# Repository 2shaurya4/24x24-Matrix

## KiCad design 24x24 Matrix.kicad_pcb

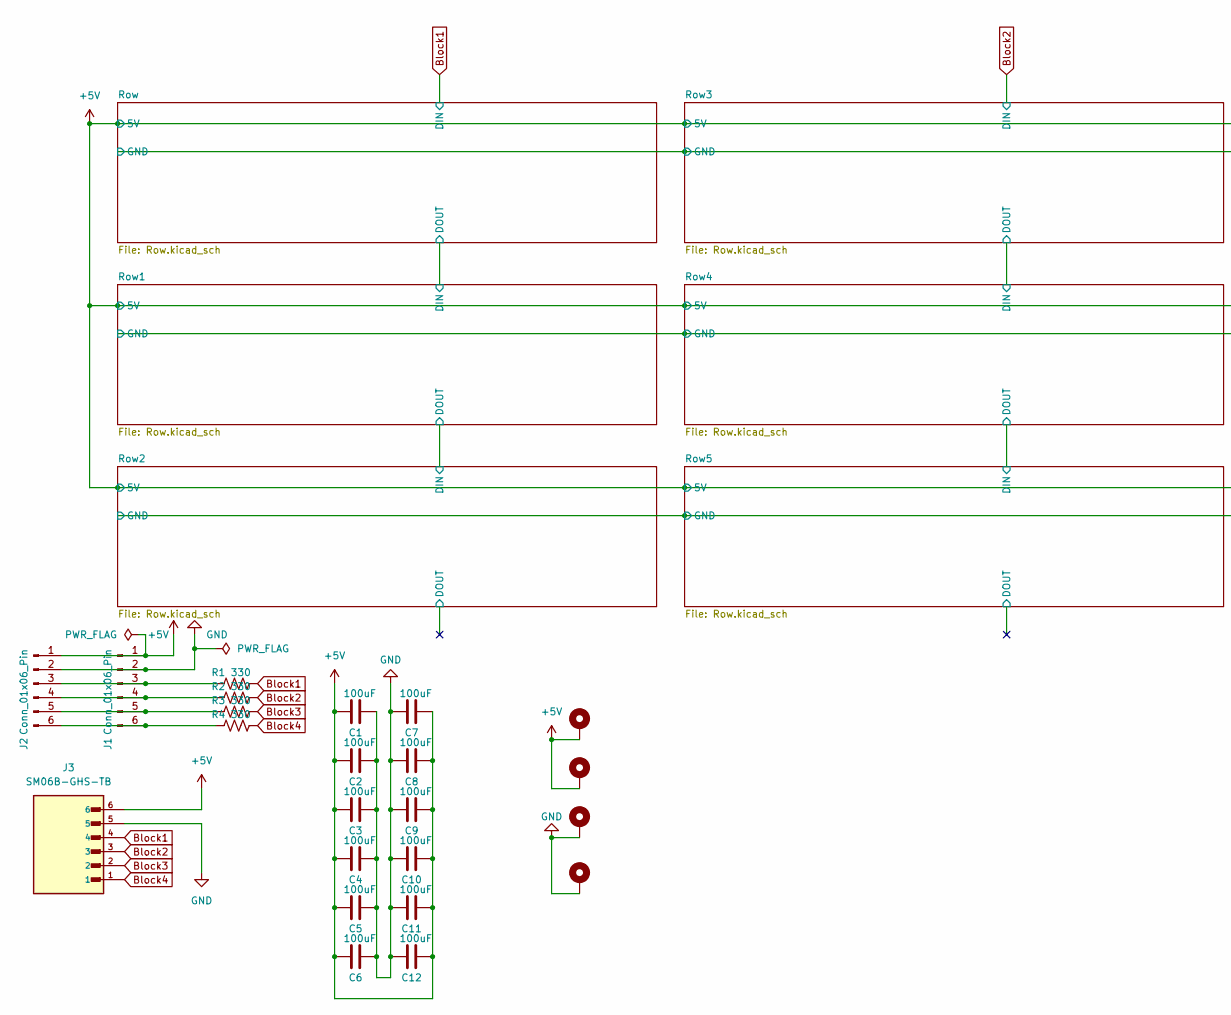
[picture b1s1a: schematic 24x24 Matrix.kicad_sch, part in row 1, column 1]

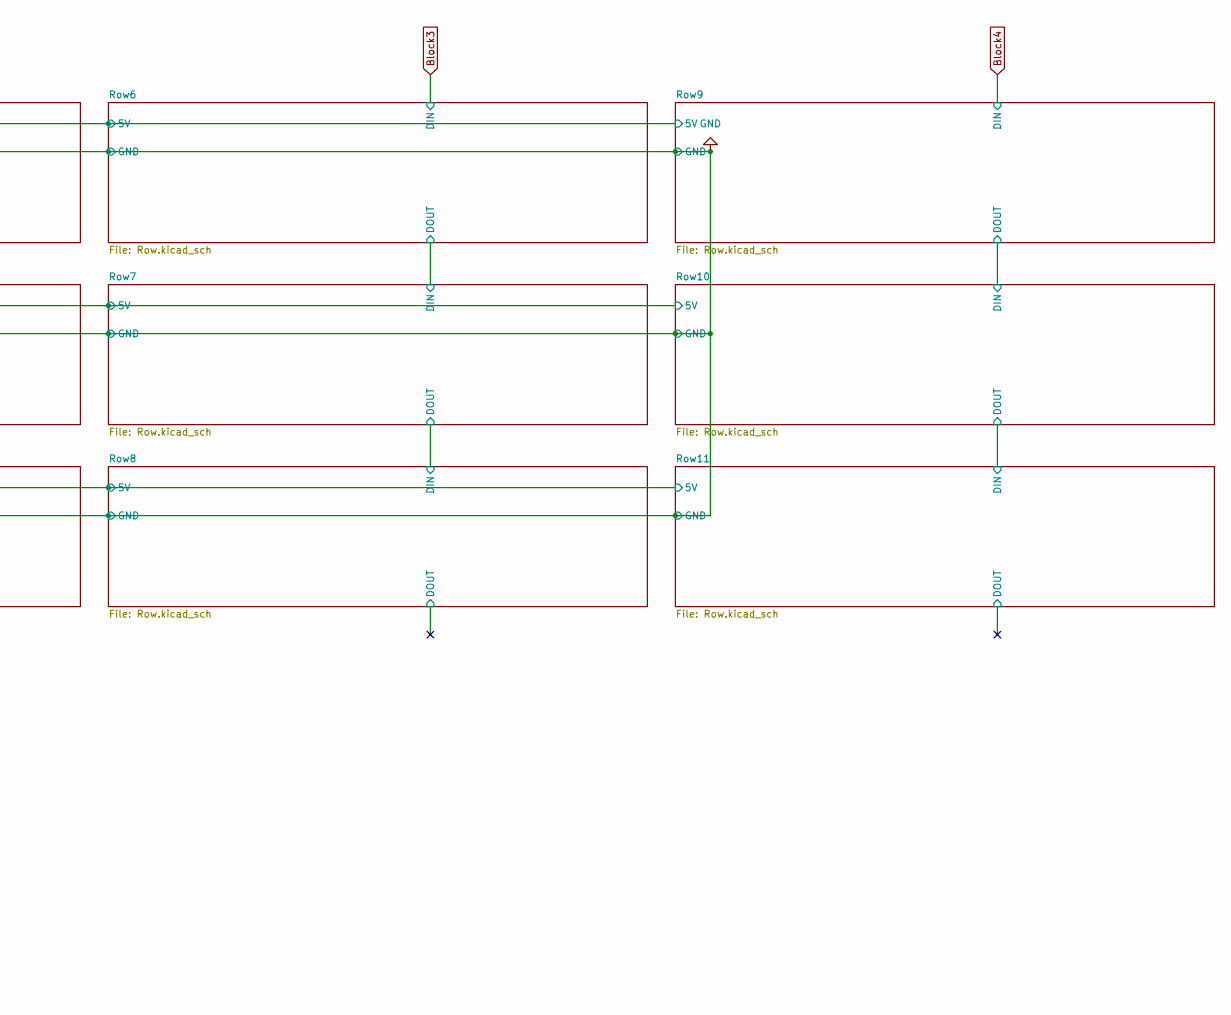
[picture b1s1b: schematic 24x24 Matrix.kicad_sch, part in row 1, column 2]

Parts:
C1, C2, C3, C4, C5, C6, C7, C8, C9, C10, C11, C12: 100uF; C_1206_3216Metric
H1, H2, H3, H4: MountingHole_Pad; MountingHole_2.7mm_M2.5_Pad_Via
J1, J2: Conn_01x06_Pin; PinHeader_1x06_P2.54mm_Vertical
J3: SM06B-GHS-TB; JST_SM06B-GHS-TB
R1, R2, R3, R4: 330; R_0402_1005Metric

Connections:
+5V: C1.1, C2.1, C3.1, C4.1, C5.1, C6.1, C7.2, C8.2, C9.2, C10.2, C11.2, C12.2, H1.1 (1_1), H2.1 (1_1), J1.1, J2.1, J3.6; also elsewhere on the board
Block1: J3.4, R1.2; also elsewhere on the board
Block2: J3.3, R2.2; also elsewhere on the board
Block3: J3.2, R3.2; also elsewhere on the board
Block4: J3.1, R4.2; also elsewhere on the board
GND: C1.2, C2.2, C3.2, C4.2, C5.2, C6.2, C7.1, C8.1, C9.1, C10.1, C11.1, C12.1, H3.1 (1_1), H4.1 (1_1), J1.2, J2.2, J3.5; also elsewhere on the board
unnamed: J1.3, J2.3, R1.1
unnamed: J1.4, J2.4, R2.1
unnamed: J1.5, J2.5, R3.1
unnamed: J1.6, J2.6, R4.1

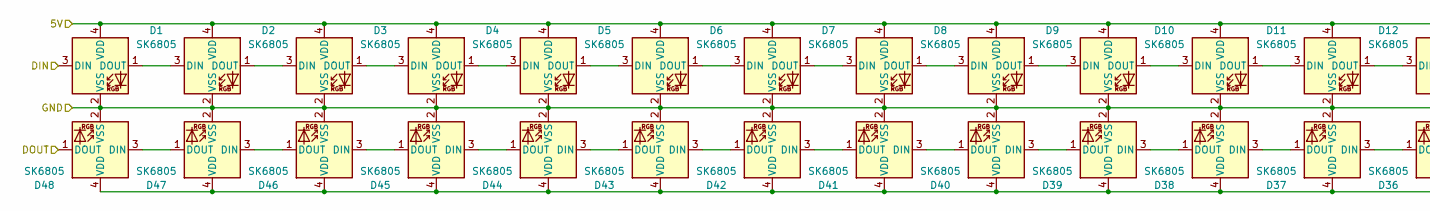
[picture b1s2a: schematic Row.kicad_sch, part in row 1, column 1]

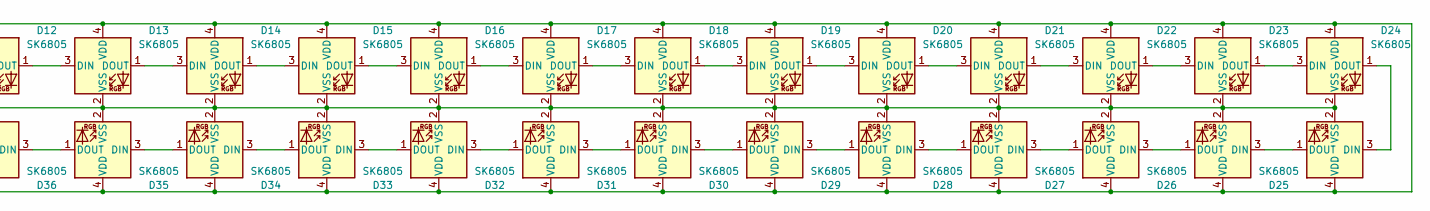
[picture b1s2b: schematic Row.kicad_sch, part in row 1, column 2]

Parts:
D1, D2, D3, D4, D5, D6, D7, D8, D9, D10, D11, D12, D13, D14, D15, D16, D17, D18, D19, D20, D21, D22, D23, D24, D25, D26, D27, D28, D29, D30, D31, D32, D33, D34, D35, D36, D37, D38, D39, D40, D41, D42, D43, D44, D45, D46, D47, D48: SK6805; LED_SK6812_EC15_1.5x1.5mm

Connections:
+5V: D1.4 (VDD), D2.4 (VDD), D3.4 (VDD), D4.4 (VDD), D5.4 (VDD), D6.4 (VDD), D7.4 (VDD), D8.4 (VDD), D9.4 (VDD), D10.4 (VDD), D11.4 (VDD), D12.4 (VDD), D13.4 (VDD), D14.4 (VDD), D15.4 (VDD), D16.4 (VDD), D17.4 (VDD), D18.4 (VDD), D19.4 (VDD), D20.4 (VDD), D21.4 (VDD), D22.4 (VDD), D23.4 (VDD), D24.4 (VDD), D25.4 (VDD), D26.4 (VDD), D27.4 (VDD), D28.4 (VDD), D29.4 (VDD), D30.4 (VDD), D31.4 (VDD), D32.4 (VDD), D33.4 (VDD), D34.4 (VDD), D35.4 (VDD), D36.4 (VDD), D37.4 (VDD), D38.4 (VDD), D39.4 (VDD), D40.4 (VDD), D41.4 (VDD), D42.4 (VDD), D43.4 (VDD), D44.4 (VDD), D45.4 (VDD), D46.4 (VDD), D47.4 (VDD), D48.4 (VDD); also elsewhere on the board
/Row/DOUT: D48.1 (DOUT); also elsewhere on the board
Block1: D1.3 (DIN); also elsewhere on the board
GND: D1.2 (VSS), D2.2 (VSS), D3.2 (VSS), D4.2 (VSS), D5.2 (VSS), D6.2 (VSS), D7.2 (VSS), D8.2 (VSS), D9.2 (VSS), D10.2 (VSS), D11.2 (VSS), D12.2 (VSS), D13.2 (VSS), D14.2 (VSS), D15.2 (VSS), D16.2 (VSS), D17.2 (VSS), D18.2 (VSS), D19.2 (VSS), D20.2 (VSS), D21.2 (VSS), D22.2 (VSS), D23.2 (VSS), D24.2 (VSS), D25.2 (VSS), D26.2 (VSS), D27.2 (VSS), D28.2 (VSS), D29.2 (VSS), D30.2 (VSS), D31.2 (VSS), D32.2 (VSS), D33.2 (VSS), D34.2 (VSS), D35.2 (VSS), D36.2 (VSS), D37.2 (VSS), D38.2 (VSS), D39.2 (VSS), D40.2 (VSS), D41.2 (VSS), D42.2 (VSS), D43.2 (VSS), D44.2 (VSS), D45.2 (VSS), D46.2 (VSS), D47.2 (VSS), D48.2 (VSS); also elsewhere on the board
unnamed: D1.1 (DOUT), D2.3 (DIN)
unnamed: D2.1 (DOUT), D3.3 (DIN)
unnamed: D3.1 (DOUT), D4.3 (DIN)
unnamed: D4.1 (DOUT), D5.3 (DIN)
unnamed: D5.1 (DOUT), D6.3 (DIN)
unnamed: D6.1 (DOUT), D7.3 (DIN)
unnamed: D7.1 (DOUT), D8.3 (DIN)
unnamed: D8.1 (DOUT), D9.3 (DIN)
unnamed: D9.1 (DOUT), D10.3 (DIN)
unnamed: D10.1 (DOUT), D11.3 (DIN)
unnamed: D11.1 (DOUT), D12.3 (DIN)
unnamed: D12.1 (DOUT), D13.3 (DIN)
unnamed: D13.1 (DOUT), D14.3 (DIN)
unnamed: D14.1 (DOUT), D15.3 (DIN)
unnamed: D15.1 (DOUT), D16.3 (DIN)
unnamed: D16.1 (DOUT), D17.3 (DIN)
unnamed: D17.1 (DOUT), D18.3 (DIN)
unnamed: D18.1 (DOUT), D19.3 (DIN)
unnamed: D19.1 (DOUT), D20.3 (DIN)
unnamed: D20.1 (DOUT), D21.3 (DIN)
unnamed: D21.1 (DOUT), D22.3 (DIN)
unnamed: D22.1 (DOUT), D23.3 (DIN)
unnamed: D23.1 (DOUT), D24.3 (DIN)
unnamed: D24.1 (DOUT), D25.3 (DIN)
unnamed: D25.1 (DOUT), D26.3 (DIN)
unnamed: D26.1 (DOUT), D27.3 (DIN)
unnamed: D27.1 (DOUT), D28.3 (DIN)
unnamed: D28.1 (DOUT), D29.3 (DIN)
unnamed: D29.1 (DOUT), D30.3 (DIN)
unnamed: D30.1 (DOUT), D31.3 (DIN)
unnamed: D31.1 (DOUT), D32.3 (DIN)
unnamed: D32.1 (DOUT), D33.3 (DIN)
unnamed: D33.1 (DOUT), D34.3 (DIN)
unnamed: D34.1 (DOUT), D35.3 (DIN)
unnamed: D35.1 (DOUT), D36.3 (DIN)
unnamed: D36.1 (DOUT), D37.3 (DIN)
unnamed: D37.1 (DOUT), D38.3 (DIN)
unnamed: D38.1 (DOUT), D39.3 (DIN)
unnamed: D39.1 (DOUT), D40.3 (DIN)
unnamed: D40.1 (DOUT), D41.3 (DIN)
unnamed: D41.1 (DOUT), D42.3 (DIN)
unnamed: D42.1 (DOUT), D43.3 (DIN)
unnamed: D43.1 (DOUT), D44.3 (DIN)
unnamed: D44.1 (DOUT), D45.3 (DIN)
unnamed: D45.1 (DOUT), D46.3 (DIN)
unnamed: D46.1 (DOUT), D47.3 (DIN)
unnamed: D47.1 (DOUT), D48.3 (DIN)

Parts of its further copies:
D49, D50, D51, D52, D53, D54, D55, D56, D57, D58, D59, D60, D61, D62, D63, D64, D65, D66, D67, D68, D69, D70, D71, D72, D73, D74, D75, D76, D77, D78, D79, D80, D81, D82, D83, D84, D85, D86, D87, D88, D89, D90, D91, D92, D93, D94, D95, D96, D97, D98, D99, D100, D101, D102, D103, D104, D105, D106, D107, D108, D109, D110, D111, D112, D113, D114, D115, D116, D117, D118, D119, D120, D121, D122, D123, D124, D125, D126, D127, D128, D129, D130, D131, D132, D133, D134, D135, D136, D137, D138, D139, D140, D141, D142, D143, D144, D145, D146, D147, D148, D149, D150, D151, D152, D153, D154, D155, D156, D157, D158, D159, D160, D161, D162, D163, D164, D165, D166, D167, D168, D169, D170, D171, D172, D173, D174, D175, D176, D177, D178, D179, D180, D181, D182, D183, D184, D185, D186, D187, D188, D189, D190, D191, D192, D193, D194, D195, D196, D197, D198, D199, D200, D201, D202, D203, D204, D205, D206, D207, D208, D209, D210, D211, D212, D213, D214, D215, D216, D217, D218, D219, D220, D221, D222, D223, D224, D225, D226, D227, D228, D229, D230, D231, D232, D233, D234, D235, D236, D237, D238, D239, D240, D241, D242, D243, D244, D245, D246, D247, D248, D249, D250, D251, D252, D253, D254, D255, D256, D257, D258, D259, D260, D261, D262, D263, D264, D265, D266, D267, D268, D269, D270, D271, D272, D273, D274, D275, D276, D277, D278, D279, D280, D281, D282, D283, D284, D285, D286, D287, D288, D289, D290, D291, D292, D293, D294, D295, D296, D297, D298, D299, D300, D301, D302, D303, D304, D305, D306, D307, D308, D309, D310, D311, D312, D313, D314, D315, D316, D317, D318, D319, D320, D321, D322, D323, D324, D325, D326, D327, D328, D329, D330, D331, D332, D333, D334, D335, D336, D337, D338, D339, D340, D341, D342, D343, D344, D345, D346, D347, D348, D349, D350, D351, D352, D353, D354, D355, D356, D357, D358, D359, D360, D361, D362, D363, D364, D365, D366, D367, D368, D369, D370, D371, D372, D373, D374, D375, D376, D377, D378, D379, D380, D381, D382, D383, D384, D385, D386, D387, D388, D389, D390, D391, D392, D393, D394, D395, D396, D397, D398, D399, D400, D401, D402, D403, D404, D405, D406, D407, D408, D409, D410, D411, D412, D413, D414, D415, D416, D417, D418, D419, D420, D421, D422, D423, D424, D425, D426, D427, D428, D429, D430, D431, D432, D433, D434, D435, D436, D437, D438, D439, D440, D441, D442, D443, D444, D445, D446, D447, D448, D449, D450, D451, D452, D453, D454, D455, D456, D457, D458, D459, D460, D461, D462, D463, D464, D465, D466, D467, D468, D469, D470, D471, D472, D473, D474, D475, D476, D477, D478, D479, D480, D481, D482, D483, D484, D485, D486, D487, D488, D489, D490, D491, D492, D493, D494, D495, D496, D497, D498, D499, D500, D501, D502, D503, D504, D505, D506, D507, D508, D509, D510, D511, D512, D513, D514, D515, D516, D517, D518, D519, D520, D521, D522, D523, D524, D525, D526, D527, D528, D529, D530, D531, D532, D533, D534, D535, D536, D537, D538, D539, D540, D541, D542, D543, D544, D545, D546, D547, D548, D549, D550, D551, D552, D553, D554, D555, D556, D557, D558, D559, D560, D561, D562, D563, D564, D565, D566, D567, D568, D569, D570, D571, D572, D573, D574, D575, D576: SK6805; LED_SK6812_EC15_1.5x1.5mm

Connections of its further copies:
+5V: D49.4 (VDD), D50.4 (VDD), D51.4 (VDD), D52.4 (VDD), D53.4 (VDD), D54.4 (VDD), D55.4 (VDD), D56.4 (VDD), D57.4 (VDD), D58.4 (VDD), D59.4 (VDD), D60.4 (VDD), D61.4 (VDD), D62.4 (VDD), D63.4 (VDD), D64.4 (VDD), D65.4 (VDD), D66.4 (VDD), D67.4 (VDD), D68.4 (VDD), D69.4 (VDD), D70.4 (VDD), D71.4 (VDD), D72.4 (VDD), D73.4 (VDD), D74.4 (VDD), D75.4 (VDD), D76.4 (VDD), D77.4 (VDD), D78.4 (VDD), D79.4 (VDD), D80.4 (VDD), D81.4 (VDD), D82.4 (VDD), D83.4 (VDD), D84.4 (VDD), D85.4 (VDD), D86.4 (VDD), D87.4 (VDD), D88.4 (VDD), D89.4 (VDD), D90.4 (VDD), D91.4 (VDD), D92.4 (VDD), D93.4 (VDD), D94.4 (VDD), D95.4 (VDD), D96.4 (VDD), D97.4 (VDD), D98.4 (VDD), D99.4 (VDD), D100.4 (VDD), D101.4 (VDD), D102.4 (VDD), D103.4 (VDD), D104.4 (VDD), D105.4 (VDD), D106.4 (VDD), D107.4 (VDD), D108.4 (VDD), D109.4 (VDD), D110.4 (VDD), D111.4 (VDD), D112.4 (VDD), D113.4 (VDD), D114.4 (VDD), D115.4 (VDD), D116.4 (VDD), D117.4 (VDD), D118.4 (VDD), D119.4 (VDD), D120.4 (VDD), D121.4 (VDD), D122.4 (VDD), D123.4 (VDD), D124.4 (VDD), D125.4 (VDD), D126.4 (VDD), D127.4 (VDD), D128.4 (VDD)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; also elsewhere on the board
/Row1/DOUT: D50.1 (DOUT), D97.3 (DIN)
/Row2/DOUT: D98.1 (DOUT)
/Row3/DOUT: D146.1 (DOUT), D193.3 (DIN)
/Row4/DOUT: D194.1 (DOUT), D241.3 (DIN)
/Row5/DOUT: D242.1 (DOUT)
/Row6/DOUT: D290.1 (DOUT), D337.3 (DIN)
/Row7/DOUT: D338.1 (DOUT), D385.3 (DIN)
/Row8/DOUT: D386.1 (DOUT)
/Row10/DIN: D434.1 (DOUT), D481.3 (DIN)
/Row10/DOUT: D482.1 (DOUT), D529.3 (DIN)
/Row11/DOUT: D530.1 (DOUT)
/Row/DOUT: D49.3 (DIN); also elsewhere on the board
Block2: D145.3 (DIN); also elsewhere on the board
Block3: D289.3 (DIN); also elsewhere on the board
Block4: D433.3 (DIN); also elsewhere on the board
GND: D49.2 (VSS), D50.2 (VSS), D51.2 (VSS), D52.2 (VSS), D53.2 (VSS), D54.2 (VSS), D55.2 (VSS), D56.2 (VSS), D57.2 (VSS), D58.2 (VSS), D59.2 (VSS), D60.2 (VSS), D61.2 (VSS), D62.2 (VSS), D63.2 (VSS), D64.2 (VSS), D65.2 (VSS), D66.2 (VSS), D67.2 (VSS), D68.2 (VSS), D69.2 (VSS), D70.2 (VSS), D71.2 (VSS), D72.2 (VSS), D73.2 (VSS), D74.2 (VSS), D75.2 (VSS), D76.2 (VSS), D77.2 (VSS), D78.2 (VSS), D79.2 (VSS), D80.2 (VSS), D81.2 (VSS), D82.2 (VSS), D83.2 (VSS), D84.2 (VSS), D85.2 (VSS), D86.2 (VSS), D87.2 (VSS), D88.2 (VSS), D89.2 (VSS), D90.2 (VSS), D91.2 (VSS), D92.2 (VSS), D93.2 (VSS), D94.2 (VSS), D95.2 (VSS), D96.2 (VSS), D97.2 (VSS), D98.2 (VSS), D99.2 (VSS), D100.2 (VSS), D101.2 (VSS), D102.2 (VSS), D103.2 (VSS), D104.2 (VSS), D105.2 (VSS), D106.2 (VSS), D107.2 (VSS), D108.2 (VSS), D109.2 (VSS), D110.2 (VSS), D111.2 (VSS), D112.2 (VSS), D113.2 (VSS), D114.2 (VSS), D115.2 (VSS), D116.2 (VSS), D117.2 (VSS), D118.2 (VSS), D119.2 (VSS), D120.2 (VSS), D121.2 (VSS), D122.2 (VSS), D123.2 (VSS), D124.2 (VSS), D125.2 (VSS), D126.2 (VSS), D127.2 (VSS), D128.2 (VSS)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; also elsewhere on the board
unnamed: D49.1 (DOUT), D51.3 (DIN)
unnamed: D50.3 (DIN), D52.1 (DOUT)
unnamed: D51.1 (DOUT), D53.3 (DIN)
unnamed: D52.3 (DIN), D54.1 (DOUT)
unnamed: D53.1 (DOUT), D55.3 (DIN)
unnamed: D54.3 (DIN), D56.1 (DOUT)
unnamed: D55.1 (DOUT), D57.3 (DIN)
unnamed: D56.3 (DIN), D58.1 (DOUT)
unnamed: D57.1 (DOUT), D59.3 (DIN)
unnamed: D58.3 (DIN), D60.1 (DOUT)
unnamed: D59.1 (DOUT), D61.3 (DIN)
unnamed: D60.3 (DIN), D62.1 (DOUT)
unnamed: D61.1 (DOUT), D63.3 (DIN)
unnamed: D62.3 (DIN), D64.1 (DOUT)
unnamed: D63.1 (DOUT), D65.3 (DIN)
unnamed: D64.3 (DIN), D66.1 (DOUT)
unnamed: D65.1 (DOUT), D67.3 (DIN)
unnamed: D66.3 (DIN), D68.1 (DOUT)
unnamed: D67.1 (DOUT), D69.3 (DIN)
unnamed: D68.3 (DIN), D70.1 (DOUT)
unnamed: D69.1 (DOUT), D71.3 (DIN)
unnamed: D70.3 (DIN), D72.1 (DOUT)
unnamed: D71.1 (DOUT), D73.3 (DIN)
unnamed: D72.3 (DIN), D74.1 (DOUT)
unnamed: D73.1 (DOUT), D75.3 (DIN)
unnamed: D74.3 (DIN), D76.1 (DOUT)
unnamed: D75.1 (DOUT), D77.3 (DIN)
unnamed: D76.3 (DIN), D78.1 (DOUT)
unnamed: D77.1 (DOUT), D79.3 (DIN)
unnamed: D78.3 (DIN), D80.1 (DOUT)
unnamed: D79.1 (DOUT), D81.3 (DIN)
unnamed: D80.3 (DIN), D82.1 (DOUT)
unnamed: D81.1 (DOUT), D83.3 (DIN)
unnamed: D82.3 (DIN), D84.1 (DOUT)
unnamed: D83.1 (DOUT), D85.3 (DIN)
unnamed: D84.3 (DIN), D86.1 (DOUT)
unnamed: D85.1 (DOUT), D87.3 (DIN)
unnamed: D86.3 (DIN), D88.1 (DOUT)
unnamed: D87.1 (DOUT), D89.3 (DIN)
unnamed: D88.3 (DIN), D90.1 (DOUT)
unnamed: D89.1 (DOUT), D91.3 (DIN)
unnamed: D90.3 (DIN), D92.1 (DOUT)
unnamed: D91.1 (DOUT), D93.3 (DIN)
unnamed: D92.3 (DIN), D94.1 (DOUT)
unnamed: D93.1 (DOUT), D95.3 (DIN)
unnamed: D94.3 (DIN), D96.1 (DOUT)
unnamed: D95.1 (DOUT), D96.3 (DIN)
unnamed: D97.1 (DOUT), D99.3 (DIN)
unnamed: D100.3 (DIN), D102.1 (DOUT)
unnamed: D98.3 (DIN), D100.1 (DOUT)
unnamed: D99.1 (DOUT), D101.3 (DIN)
unnamed: D101.1 (DOUT), D103.3 (DIN)
unnamed: D102.3 (DIN), D104.1 (DOUT)
unnamed: D103.1 (DOUT), D105.3 (DIN)
unnamed: D104.3 (DIN), D106.1 (DOUT)
unnamed: D105.1 (DOUT), D107.3 (DIN)
unnamed: D106.3 (DIN), D108.1 (DOUT)
unnamed: D107.1 (DOUT), D109.3 (DIN)
unnamed: D108.3 (DIN), D110.1 (DOUT)
unnamed: D109.1 (DOUT), D111.3 (DIN)
unnamed: D110.3 (DIN), D112.1 (DOUT)
unnamed: D111.1 (DOUT), D113.3 (DIN)
unnamed: D112.3 (DIN), D114.1 (DOUT)
unnamed: D113.1 (DOUT), D115.3 (DIN)
unnamed: D114.3 (DIN), D116.1 (DOUT)
unnamed: D115.1 (DOUT), D117.3 (DIN)
unnamed: D116.3 (DIN), D118.1 (DOUT)
unnamed: D117.1 (DOUT), D119.3 (DIN)
unnamed: D118.3 (DIN), D120.1 (DOUT)
unnamed: D119.1 (DOUT), D121.3 (DIN)
unnamed: D120.3 (DIN), D122.1 (DOUT)
unnamed: D121.1 (DOUT), D123.3 (DIN)
unnamed: D122.3 (DIN), D124.1 (DOUT)
unnamed: D123.1 (DOUT), D125.3 (DIN)
unnamed: D124.3 (DIN), D126.1 (DOUT)
unnamed: D125.1 (DOUT), D127.3 (DIN)
unnamed: D126.3 (DIN), D128.1 (DOUT)
unnamed: D127.1 (DOUT), D129.3 (DIN)
unnamed: D128.3 (DIN), D130.1 (DOUT)
unnamed: D129.1 (DOUT), D131.3 (DIN)
unnamed: D130.3 (DIN), D132.1 (DOUT)
unnamed: D131.1 (DOUT), D133.3 (DIN)
unnamed: D132.3 (DIN), D134.1 (DOUT)
unnamed: D133.1 (DOUT), D135.3 (DIN)
unnamed: D134.3 (DIN), D136.1 (DOUT)
unnamed: D135.1 (DOUT), D137.3 (DIN)
unnamed: D136.3 (DIN), D138.1 (DOUT)
unnamed: D137.1 (DOUT), D139.3 (DIN)
unnamed: D138.3 (DIN), D140.1 (DOUT)
unnamed: D139.1 (DOUT), D141.3 (DIN)
unnamed: D140.3 (DIN), D142.1 (DOUT)
unnamed: D141.1 (DOUT), D143.3 (DIN)
unnamed: D142.3 (DIN), D144.1 (DOUT)
unnamed: D143.1 (DOUT), D144.3 (DIN)
unnamed: D145.1 (DOUT), D147.3 (DIN)
unnamed: D146.3 (DIN), D148.1 (DOUT)
unnamed: D147.1 (DOUT), D149.3 (DIN)
unnamed: D148.3 (DIN), D150.1 (DOUT)
unnamed: D149.1 (DOUT), D151.3 (DIN)
unnamed: D150.3 (DIN), D152.1 (DOUT)
unnamed: D151.1 (DOUT), D153.3 (DIN)
unnamed: D152.3 (DIN), D154.1 (DOUT)
unnamed: D153.1 (DOUT), D155.3 (DIN)
unnamed: D154.3 (DIN), D156.1 (DOUT)
unnamed: D155.1 (DOUT), D157.3 (DIN)
unnamed: D156.3 (DIN), D158.1 (DOUT)
unnamed: D157.1 (DOUT), D159.3 (DIN)
unnamed: D158.3 (DIN), D160.1 (DOUT)
unnamed: D159.1 (DOUT), D161.3 (DIN)
unnamed: D160.3 (DIN), D162.1 (DOUT)
unnamed: D161.1 (DOUT), D163.3 (DIN)
unnamed: D162.3 (DIN), D164.1 (DOUT)
unnamed: D163.1 (DOUT), D165.3 (DIN)
unnamed: D164.3 (DIN), D166.1 (DOUT)
unnamed: D165.1 (DOUT), D167.3 (DIN)
unnamed: D166.3 (DIN), D168.1 (DOUT)
unnamed: D167.1 (DOUT), D169.3 (DIN)
unnamed: D168.3 (DIN), D170.1 (DOUT)
unnamed: D169.1 (DOUT), D171.3 (DIN)
unnamed: D170.3 (DIN), D172.1 (DOUT)
unnamed: D171.1 (DOUT), D173.3 (DIN)
unnamed: D172.3 (DIN), D174.1 (DOUT)
unnamed: D173.1 (DOUT), D175.3 (DIN)
unnamed: D174.3 (DIN), D176.1 (DOUT)
unnamed: D175.1 (DOUT), D177.3 (DIN)
unnamed: D176.3 (DIN), D178.1 (DOUT)
unnamed: D177.1 (DOUT), D179.3 (DIN)
unnamed: D178.3 (DIN), D180.1 (DOUT)
unnamed: D179.1 (DOUT), D181.3 (DIN)
unnamed: D180.3 (DIN), D182.1 (DOUT)
unnamed: D181.1 (DOUT), D183.3 (DIN)
unnamed: D182.3 (DIN), D184.1 (DOUT)
unnamed: D183.1 (DOUT), D185.3 (DIN)
unnamed: D184.3 (DIN), D186.1 (DOUT)
unnamed: D185.1 (DOUT), D187.3 (DIN)
unnamed: D186.3 (DIN), D188.1 (DOUT)
unnamed: D187.1 (DOUT), D189.3 (DIN)
unnamed: D188.3 (DIN), D190.1 (DOUT)
unnamed: D189.1 (DOUT), D191.3 (DIN)
unnamed: D190.3 (DIN), D192.1 (DOUT)
unnamed: D191.1 (DOUT), D192.3 (DIN)
unnamed: D193.1 (DOUT), D195.3 (DIN)
unnamed: D194.3 (DIN), D196.1 (DOUT)
unnamed: D195.1 (DOUT), D197.3 (DIN)
unnamed: D196.3 (DIN), D198.1 (DOUT)
unnamed: D197.1 (DOUT), D199.3 (DIN)
unnamed: D198.3 (DIN), D200.1 (DOUT)
unnamed: D199.1 (DOUT), D201.3 (DIN)
unnamed: D200.3 (DIN), D202.1 (DOUT)
unnamed: D201.1 (DOUT), D203.3 (DIN)
unnamed: D202.3 (DIN), D204.1 (DOUT)
unnamed: D203.1 (DOUT), D205.3 (DIN)
unnamed: D204.3 (DIN), D206.1 (DOUT)
unnamed: D205.1 (DOUT), D207.3 (DIN)
unnamed: D206.3 (DIN), D208.1 (DOUT)
unnamed: D207.1 (DOUT), D209.3 (DIN)
unnamed: D208.3 (DIN), D210.1 (DOUT)
unnamed: D209.1 (DOUT), D211.3 (DIN)
unnamed: D210.3 (DIN), D212.1 (DOUT)
unnamed: D211.1 (DOUT), D213.3 (DIN)
unnamed: D212.3 (DIN), D214.1 (DOUT)
unnamed: D213.1 (DOUT), D215.3 (DIN)
unnamed: D214.3 (DIN), D216.1 (DOUT)
unnamed: D215.1 (DOUT), D217.3 (DIN)
unnamed: D216.3 (DIN), D218.1 (DOUT)
unnamed: D217.1 (DOUT), D219.3 (DIN)
unnamed: D218.3 (DIN), D220.1 (DOUT)
unnamed: D219.1 (DOUT), D221.3 (DIN)
unnamed: D220.3 (DIN), D222.1 (DOUT)
unnamed: D221.1 (DOUT), D223.3 (DIN)
unnamed: D222.3 (DIN), D224.1 (DOUT)
unnamed: D223.1 (DOUT), D225.3 (DIN)
unnamed: D224.3 (DIN), D226.1 (DOUT)
unnamed: D225.1 (DOUT), D227.3 (DIN)
unnamed: D226.3 (DIN), D228.1 (DOUT)
unnamed: D227.1 (DOUT), D229.3 (DIN)
unnamed: D228.3 (DIN), D230.1 (DOUT)
unnamed: D229.1 (DOUT), D231.3 (DIN)
unnamed: D230.3 (DIN), D232.1 (DOUT)
unnamed: D231.1 (DOUT), D233.3 (DIN)
unnamed: D232.3 (DIN), D234.1 (DOUT)
unnamed: D233.1 (DOUT), D235.3 (DIN)
unnamed: D234.3 (DIN), D236.1 (DOUT)
unnamed: D235.1 (DOUT), D237.3 (DIN)
unnamed: D236.3 (DIN), D238.1 (DOUT)
unnamed: D237.1 (DOUT), D239.3 (DIN)
unnamed: D238.3 (DIN), D240.1 (DOUT)
unnamed: D239.1 (DOUT), D240.3 (DIN)
unnamed: D241.1 (DOUT), D243.3 (DIN)
unnamed: D242.3 (DIN), D244.1 (DOUT)
unnamed: D243.1 (DOUT), D245.3 (DIN)
unnamed: D244.3 (DIN), D246.1 (DOUT)
unnamed: D245.1 (DOUT), D247.3 (DIN)
unnamed: D246.3 (DIN), D248.1 (DOUT)
unnamed: D247.1 (DOUT), D249.3 (DIN)
unnamed: D248.3 (DIN), D250.1 (DOUT)
unnamed: D249.1 (DOUT), D251.3 (DIN)
unnamed: D250.3 (DIN), D252.1 (DOUT)
unnamed: D251.1 (DOUT), D253.3 (DIN)
unnamed: D252.3 (DIN), D254.1 (DOUT)
unnamed: D253.1 (DOUT), D255.3 (DIN)
unnamed: D254.3 (DIN), D256.1 (DOUT)
unnamed: D255.1 (DOUT), D257.3 (DIN)
unnamed: D256.3 (DIN), D258.1 (DOUT)
unnamed: D257.1 (DOUT), D259.3 (DIN)
unnamed: D258.3 (DIN), D260.1 (DOUT)
unnamed: D259.1 (DOUT), D261.3 (DIN)
unnamed: D260.3 (DIN), D262.1 (DOUT)
unnamed: D261.1 (DOUT), D263.3 (DIN)
unnamed: D262.3 (DIN), D264.1 (DOUT)
unnamed: D263.1 (DOUT), D265.3 (DIN)
unnamed: D264.3 (DIN), D266.1 (DOUT)
unnamed: D265.1 (DOUT), D267.3 (DIN)
unnamed: D266.3 (DIN), D268.1 (DOUT)
unnamed: D267.1 (DOUT), D269.3 (DIN)
unnamed: D268.3 (DIN), D270.1 (DOUT)
unnamed: D269.1 (DOUT), D271.3 (DIN)
unnamed: D270.3 (DIN), D272.1 (DOUT)
unnamed: D271.1 (DOUT), D273.3 (DIN)
unnamed: D272.3 (DIN), D274.1 (DOUT)
unnamed: D273.1 (DOUT), D275.3 (DIN)
unnamed: D274.3 (DIN), D276.1 (DOUT)
unnamed: D275.1 (DOUT), D277.3 (DIN)
unnamed: D276.3 (DIN), D278.1 (DOUT)
unnamed: D277.1 (DOUT), D279.3 (DIN)
unnamed: D278.3 (DIN), D280.1 (DOUT)
unnamed: D279.1 (DOUT), D281.3 (DIN)
unnamed: D280.3 (DIN), D282.1 (DOUT)
unnamed: D281.1 (DOUT), D283.3 (DIN)
unnamed: D282.3 (DIN), D284.1 (DOUT)
unnamed: D283.1 (DOUT), D285.3 (DIN)
unnamed: D284.3 (DIN), D286.1 (DOUT)
unnamed: D285.1 (DOUT), D287.3 (DIN)
unnamed: D286.3 (DIN), D288.1 (DOUT)
unnamed: D287.1 (DOUT), D288.3 (DIN)
unnamed: D289.1 (DOUT), D291.3 (DIN)
unnamed: D290.3 (DIN), D292.1 (DOUT)
unnamed: D291.1 (DOUT), D293.3 (DIN)
unnamed: D292.3 (DIN), D294.1 (DOUT)
unnamed: D293.1 (DOUT), D295.3 (DIN)
unnamed: D294.3 (DIN), D296.1 (DOUT)
unnamed: D295.1 (DOUT), D297.3 (DIN)
unnamed: D296.3 (DIN), D298.1 (DOUT)
unnamed: D297.1 (DOUT), D299.3 (DIN)
unnamed: D298.3 (DIN), D300.1 (DOUT)
unnamed: D299.1 (DOUT), D301.3 (DIN)
unnamed: D300.3 (DIN), D302.1 (DOUT)
unnamed: D301.1 (DOUT), D303.3 (DIN)
unnamed: D302.3 (DIN), D304.1 (DOUT)
unnamed: D303.1 (DOUT), D305.3 (DIN)
unnamed: D304.3 (DIN), D306.1 (DOUT)
unnamed: D305.1 (DOUT), D307.3 (DIN)
unnamed: D306.3 (DIN), D308.1 (DOUT)
unnamed: D307.1 (DOUT), D309.3 (DIN)
unnamed: D308.3 (DIN), D310.1 (DOUT)
unnamed: D309.1 (DOUT), D311.3 (DIN)
unnamed: D310.3 (DIN), D312.1 (DOUT)
unnamed: D311.1 (DOUT), D313.3 (DIN)
unnamed: D312.3 (DIN), D314.1 (DOUT)
unnamed: D313.1 (DOUT), D315.3 (DIN)
unnamed: D314.3 (DIN), D316.1 (DOUT)
unnamed: D315.1 (DOUT), D317.3 (DIN)
unnamed: D316.3 (DIN), D318.1 (DOUT)
unnamed: D317.1 (DOUT), D319.3 (DIN)
unnamed: D318.3 (DIN), D320.1 (DOUT)
unnamed: D319.1 (DOUT), D321.3 (DIN)
unnamed: D320.3 (DIN), D322.1 (DOUT)
unnamed: D321.1 (DOUT), D323.3 (DIN)
unnamed: D322.3 (DIN), D324.1 (DOUT)
unnamed: D323.1 (DOUT), D325.3 (DIN)
unnamed: D324.3 (DIN), D326.1 (DOUT)
unnamed: D325.1 (DOUT), D327.3 (DIN)
unnamed: D326.3 (DIN), D328.1 (DOUT)
unnamed: D327.1 (DOUT), D329.3 (DIN)
unnamed: D328.3 (DIN), D330.1 (DOUT)
unnamed: D329.1 (DOUT), D331.3 (DIN)
unnamed: D330.3 (DIN), D332.1 (DOUT)
unnamed: D331.1 (DOUT), D333.3 (DIN)
unnamed: D332.3 (DIN), D334.1 (DOUT)
unnamed: D333.1 (DOUT), D335.3 (DIN)
unnamed: D334.3 (DIN), D336.1 (DOUT)
unnamed: D335.1 (DOUT), D336.3 (DIN)
unnamed: D337.1 (DOUT), D339.3 (DIN)
unnamed: D338.3 (DIN), D340.1 (DOUT)
unnamed: D339.1 (DOUT), D341.3 (DIN)
unnamed: D340.3 (DIN), D342.1 (DOUT)
unnamed: D341.1 (DOUT), D343.3 (DIN)
unnamed: D342.3 (DIN), D344.1 (DOUT)
unnamed: D343.1 (DOUT), D345.3 (DIN)
unnamed: D344.3 (DIN), D346.1 (DOUT)
unnamed: D345.1 (DOUT), D347.3 (DIN)
unnamed: D346.3 (DIN), D348.1 (DOUT)
unnamed: D347.1 (DOUT), D349.3 (DIN)
unnamed: D348.3 (DIN), D350.1 (DOUT)
unnamed: D349.1 (DOUT), D351.3 (DIN)
unnamed: D350.3 (DIN), D352.1 (DOUT)
unnamed: D351.1 (DOUT), D353.3 (DIN)
unnamed: D352.3 (DIN), D354.1 (DOUT)
unnamed: D353.1 (DOUT), D355.3 (DIN)
unnamed: D354.3 (DIN), D356.1 (DOUT)
unnamed: D355.1 (DOUT), D357.3 (DIN)
unnamed: D356.3 (DIN), D358.1 (DOUT)
unnamed: D357.1 (DOUT), D359.3 (DIN)
unnamed: D358.3 (DIN), D360.1 (DOUT)
unnamed: D359.1 (DOUT), D361.3 (DIN)
unnamed: D360.3 (DIN), D362.1 (DOUT)
unnamed: D361.1 (DOUT), D363.3 (DIN)
unnamed: D362.3 (DIN), D364.1 (DOUT)
unnamed: D363.1 (DOUT), D365.3 (DIN)
unnamed: D364.3 (DIN), D366.1 (DOUT)
unnamed: D365.1 (DOUT), D367.3 (DIN)
unnamed: D366.3 (DIN), D368.1 (DOUT)
unnamed: D367.1 (DOUT), D369.3 (DIN)
unnamed: D368.3 (DIN), D370.1 (DOUT)
unnamed: D369.1 (DOUT), D371.3 (DIN)
unnamed: D370.3 (DIN), D372.1 (DOUT)
unnamed: D371.1 (DOUT), D373.3 (DIN)
unnamed: D372.3 (DIN), D374.1 (DOUT)
unnamed: D373.1 (DOUT), D375.3 (DIN)
unnamed: D374.3 (DIN), D376.1 (DOUT)
unnamed: D375.1 (DOUT), D377.3 (DIN)
unnamed: D376.3 (DIN), D378.1 (DOUT)
unnamed: D377.1 (DOUT), D379.3 (DIN)
unnamed: D378.3 (DIN), D380.1 (DOUT)
unnamed: D379.1 (DOUT), D381.3 (DIN)
unnamed: D380.3 (DIN), D382.1 (DOUT)
unnamed: D381.1 (DOUT), D383.3 (DIN)
unnamed: D382.3 (DIN), D384.1 (DOUT)
unnamed: D383.1 (DOUT), D384.3 (DIN)
unnamed: D385.1 (DOUT), D387.3 (DIN)
unnamed: D386.3 (DIN), D388.1 (DOUT)
unnamed: D387.1 (DOUT), D389.3 (DIN)
unnamed: D388.3 (DIN), D390.1 (DOUT)
unnamed: D389.1 (DOUT), D391.3 (DIN)
unnamed: D390.3 (DIN), D392.1 (DOUT)
unnamed: D391.1 (DOUT), D393.3 (DIN)
unnamed: D392.3 (DIN), D394.1 (DOUT)
unnamed: D393.1 (DOUT), D395.3 (DIN)
unnamed: D394.3 (DIN), D396.1 (DOUT)
unnamed: D395.1 (DOUT), D397.3 (DIN)
unnamed: D396.3 (DIN), D398.1 (DOUT)
unnamed: D397.1 (DOUT), D399.3 (DIN)
unnamed: D398.3 (DIN), D400.1 (DOUT)
unnamed: D399.1 (DOUT), D401.3 (DIN)
unnamed: D400.3 (DIN), D402.1 (DOUT)
unnamed: D401.1 (DOUT), D403.3 (DIN)
unnamed: D402.3 (DIN), D404.1 (DOUT)
unnamed: D403.1 (DOUT), D405.3 (DIN)
unnamed: D404.3 (DIN), D406.1 (DOUT)
unnamed: D405.1 (DOUT), D407.3 (DIN)
unnamed: D406.3 (DIN), D408.1 (DOUT)
unnamed: D407.1 (DOUT), D409.3 (DIN)
unnamed: D408.3 (DIN), D410.1 (DOUT)
unnamed: D409.1 (DOUT), D411.3 (DIN)
unnamed: D410.3 (DIN), D412.1 (DOUT)
unnamed: D411.1 (DOUT), D413.3 (DIN)
unnamed: D412.3 (DIN), D414.1 (DOUT)
unnamed: D413.1 (DOUT), D415.3 (DIN)
unnamed: D414.3 (DIN), D416.1 (DOUT)
unnamed: D415.1 (DOUT), D417.3 (DIN)
unnamed: D416.3 (DIN), D418.1 (DOUT)
unnamed: D417.1 (DOUT), D419.3 (DIN)
unnamed: D418.3 (DIN), D420.1 (DOUT)
unnamed: D419.1 (DOUT), D421.3 (DIN)
unnamed: D420.3 (DIN), D422.1 (DOUT)
unnamed: D421.1 (DOUT), D423.3 (DIN)
unnamed: D422.3 (DIN), D424.1 (DOUT)
unnamed: D423.1 (DOUT), D425.3 (DIN)
unnamed: D424.3 (DIN), D426.1 (DOUT)
unnamed: D425.1 (DOUT), D427.3 (DIN)
unnamed: D426.3 (DIN), D428.1 (DOUT)
unnamed: D427.1 (DOUT), D429.3 (DIN)
unnamed: D428.3 (DIN), D430.1 (DOUT)
unnamed: D429.1 (DOUT), D431.3 (DIN)
unnamed: D430.3 (DIN), D432.1 (DOUT)
unnamed: D431.1 (DOUT), D432.3 (DIN)
unnamed: D433.1 (DOUT), D435.3 (DIN)
unnamed: D434.3 (DIN), D436.1 (DOUT)
unnamed: D435.1 (DOUT), D437.3 (DIN)
unnamed: D436.3 (DIN), D438.1 (DOUT)
unnamed: D437.1 (DOUT), D439.3 (DIN)
unnamed: D438.3 (DIN), D440.1 (DOUT)
unnamed: D439.1 (DOUT), D441.3 (DIN)
unnamed: D440.3 (DIN), D442.1 (DOUT)
unnamed: D441.1 (DOUT), D443.3 (DIN)
unnamed: D442.3 (DIN), D444.1 (DOUT)
unnamed: D443.1 (DOUT), D445.3 (DIN)
unnamed: D444.3 (DIN), D446.1 (DOUT)
unnamed: D445.1 (DOUT), D447.3 (DIN)
unnamed: D446.3 (DIN), D448.1 (DOUT)
unnamed: D447.1 (DOUT), D449.3 (DIN)
unnamed: D448.3 (DIN), D450.1 (DOUT)
unnamed: D449.1 (DOUT), D451.3 (DIN)
unnamed: D450.3 (DIN), D452.1 (DOUT)
unnamed: D451.1 (DOUT), D453.3 (DIN)
unnamed: D452.3 (DIN), D454.1 (DOUT)
unnamed: D453.1 (DOUT), D455.3 (DIN)
unnamed: D454.3 (DIN), D456.1 (DOUT)
unnamed: D455.1 (DOUT), D457.3 (DIN)
unnamed: D456.3 (DIN), D458.1 (DOUT)
unnamed: D457.1 (DOUT), D459.3 (DIN)
unnamed: D458.3 (DIN), D460.1 (DOUT)
unnamed: D459.1 (DOUT), D461.3 (DIN)
unnamed: D460.3 (DIN), D462.1 (DOUT)
unnamed: D461.1 (DOUT), D463.3 (DIN)
unnamed: D462.3 (DIN), D464.1 (DOUT)
unnamed: D463.1 (DOUT), D465.3 (DIN)
unnamed: D464.3 (DIN), D466.1 (DOUT)
unnamed: D465.1 (DOUT), D467.3 (DIN)
unnamed: D466.3 (DIN), D468.1 (DOUT)
unnamed: D467.1 (DOUT), D469.3 (DIN)
unnamed: D468.3 (DIN), D470.1 (DOUT)
unnamed: D469.1 (DOUT), D471.3 (DIN)
unnamed: D470.3 (DIN), D472.1 (DOUT)
unnamed: D471.1 (DOUT), D473.3 (DIN)
unnamed: D472.3 (DIN), D474.1 (DOUT)
unnamed: D473.1 (DOUT), D475.3 (DIN)
unnamed: D474.3 (DIN), D476.1 (DOUT)
unnamed: D475.1 (DOUT), D477.3 (DIN)
unnamed: D476.3 (DIN), D478.1 (DOUT)
unnamed: D477.1 (DOUT), D479.3 (DIN)
unnamed: D478.3 (DIN), D480.1 (DOUT)
unnamed: D479.1 (DOUT), D480.3 (DIN)
unnamed: D481.1 (DOUT), D483.3 (DIN)
unnamed: D482.3 (DIN), D484.1 (DOUT)
unnamed: D483.1 (DOUT), D485.3 (DIN)
unnamed: D484.3 (DIN), D486.1 (DOUT)
unnamed: D485.1 (DOUT), D487.3 (DIN)
unnamed: D486.3 (DIN), D488.1 (DOUT)
unnamed: D487.1 (DOUT), D489.3 (DIN)
unnamed: D488.3 (DIN), D490.1 (DOUT)
unnamed: D489.1 (DOUT), D491.3 (DIN)
unnamed: D490.3 (DIN), D492.1 (DOUT)
unnamed: D491.1 (DOUT), D493.3 (DIN)
unnamed: D492.3 (DIN), D494.1 (DOUT)
unnamed: D493.1 (DOUT), D495.3 (DIN)
unnamed: D494.3 (DIN), D496.1 (DOUT)
unnamed: D495.1 (DOUT), D497.3 (DIN)
unnamed: D496.3 (DIN), D498.1 (DOUT)
unnamed: D497.1 (DOUT), D499.3 (DIN)
unnamed: D498.3 (DIN), D500.1 (DOUT)
unnamed: D499.1 (DOUT), D501.3 (DIN)
unnamed: D500.3 (DIN), D502.1 (DOUT)
unnamed: D501.1 (DOUT), D503.3 (DIN)
unnamed: D502.3 (DIN), D504.1 (DOUT)
unnamed: D503.1 (DOUT), D505.3 (DIN)
unnamed: D504.3 (DIN), D506.1 (DOUT)
unnamed: D505.1 (DOUT), D507.3 (DIN)
unnamed: D506.3 (DIN), D508.1 (DOUT)
unnamed: D507.1 (DOUT), D509.3 (DIN)
unnamed: D508.3 (DIN), D510.1 (DOUT)
unnamed: D509.1 (DOUT), D511.3 (DIN)
unnamed: D510.3 (DIN), D512.1 (DOUT)
unnamed: D511.1 (DOUT), D513.3 (DIN)
unnamed: D512.3 (DIN), D514.1 (DOUT)
unnamed: D513.1 (DOUT), D515.3 (DIN)
unnamed: D514.3 (DIN), D516.1 (DOUT)
unnamed: D515.1 (DOUT), D517.3 (DIN)
unnamed: D516.3 (DIN), D518.1 (DOUT)
unnamed: D517.1 (DOUT), D519.3 (DIN)
unnamed: D518.3 (DIN), D520.1 (DOUT)
unnamed: D519.1 (DOUT), D521.3 (DIN)
unnamed: D520.3 (DIN), D522.1 (DOUT)
unnamed: D521.1 (DOUT), D523.3 (DIN)
unnamed: D522.3 (DIN), D524.1 (DOUT)
unnamed: D523.1 (DOUT), D525.3 (DIN)
unnamed: D524.3 (DIN), D526.1 (DOUT)
unnamed: D525.1 (DOUT), D527.3 (DIN)
unnamed: D526.3 (DIN), D528.1 (DOUT)
unnamed: D527.1 (DOUT), D528.3 (DIN)
unnamed: D529.1 (DOUT), D531.3 (DIN)
unnamed: D530.3 (DIN), D532.1 (DOUT)
unnamed: D531.1 (DOUT), D533.3 (DIN)
unnamed: D532.3 (DIN), D534.1 (DOUT)
unnamed: D533.1 (DOUT), D535.3 (DIN)
unnamed: D534.3 (DIN), D536.1 (DOUT)
unnamed: D535.1 (DOUT), D537.3 (DIN)
unnamed: D536.3 (DIN), D538.1 (DOUT)
unnamed: D537.1 (DOUT), D539.3 (DIN)
unnamed: D538.3 (DIN), D540.1 (DOUT)
unnamed: D539.1 (DOUT), D541.3 (DIN)
unnamed: D540.3 (DIN), D542.1 (DOUT)
unnamed: D541.1 (DOUT), D543.3 (DIN)
unnamed: D542.3 (DIN), D544.1 (DOUT)
unnamed: D543.1 (DOUT), D545.3 (DIN)
unnamed: D544.3 (DIN), D546.1 (DOUT)
unnamed: D545.1 (DOUT), D547.3 (DIN)
unnamed: D546.3 (DIN), D548.1 (DOUT)
unnamed: D547.1 (DOUT), D549.3 (DIN)
unnamed: D548.3 (DIN), D550.1 (DOUT)
unnamed: D549.1 (DOUT), D551.3 (DIN)
unnamed: D550.3 (DIN), D552.1 (DOUT)
unnamed: D551.1 (DOUT), D553.3 (DIN)
unnamed: D552.3 (DIN), D554.1 (DOUT)
unnamed: D553.1 (DOUT), D555.3 (DIN)
unnamed: D554.3 (DIN), D556.1 (DOUT)
unnamed: D555.1 (DOUT), D557.3 (DIN)
unnamed: D556.3 (DIN), D558.1 (DOUT)
unnamed: D557.1 (DOUT), D559.3 (DIN)
unnamed: D558.3 (DIN), D560.1 (DOUT)
unnamed: D559.1 (DOUT), D561.3 (DIN)
unnamed: D560.3 (DIN), D562.1 (DOUT)
unnamed: D561.1 (DOUT), D563.3 (DIN)
unnamed: D562.3 (DIN), D564.1 (DOUT)
unnamed: D563.1 (DOUT), D565.3 (DIN)
unnamed: D564.3 (DIN), D566.1 (DOUT)
unnamed: D565.1 (DOUT), D567.3 (DIN)
unnamed: D566.3 (DIN), D568.1 (DOUT)
unnamed: D567.1 (DOUT), D569.3 (DIN)
unnamed: D568.3 (DIN), D570.1 (DOUT)
unnamed: D569.1 (DOUT), D571.3 (DIN)
unnamed: D570.3 (DIN), D572.1 (DOUT)
unnamed: D571.1 (DOUT), D573.3 (DIN)
unnamed: D572.3 (DIN), D574.1 (DOUT)
unnamed: D573.1 (DOUT), D575.3 (DIN)
unnamed: D574.3 (DIN), D576.1 (DOUT)
unnamed: D575.1 (DOUT), D576.3 (DIN)
